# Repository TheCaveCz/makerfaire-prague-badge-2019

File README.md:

# MakerFaire Prague 2019 badge

Complete source code and schematics for MakerFaire Prague 2019 badges and other supporting devices.

*We are preparing more readme files, stay tuned*

## Few images

## Sponsorship

Badges were sponsored by [Seeed Studio](https://www.seeedstudio.com).

Výrobu badgů sponzorovalo [Seeed Studio](https://www.seeedstudio.com).

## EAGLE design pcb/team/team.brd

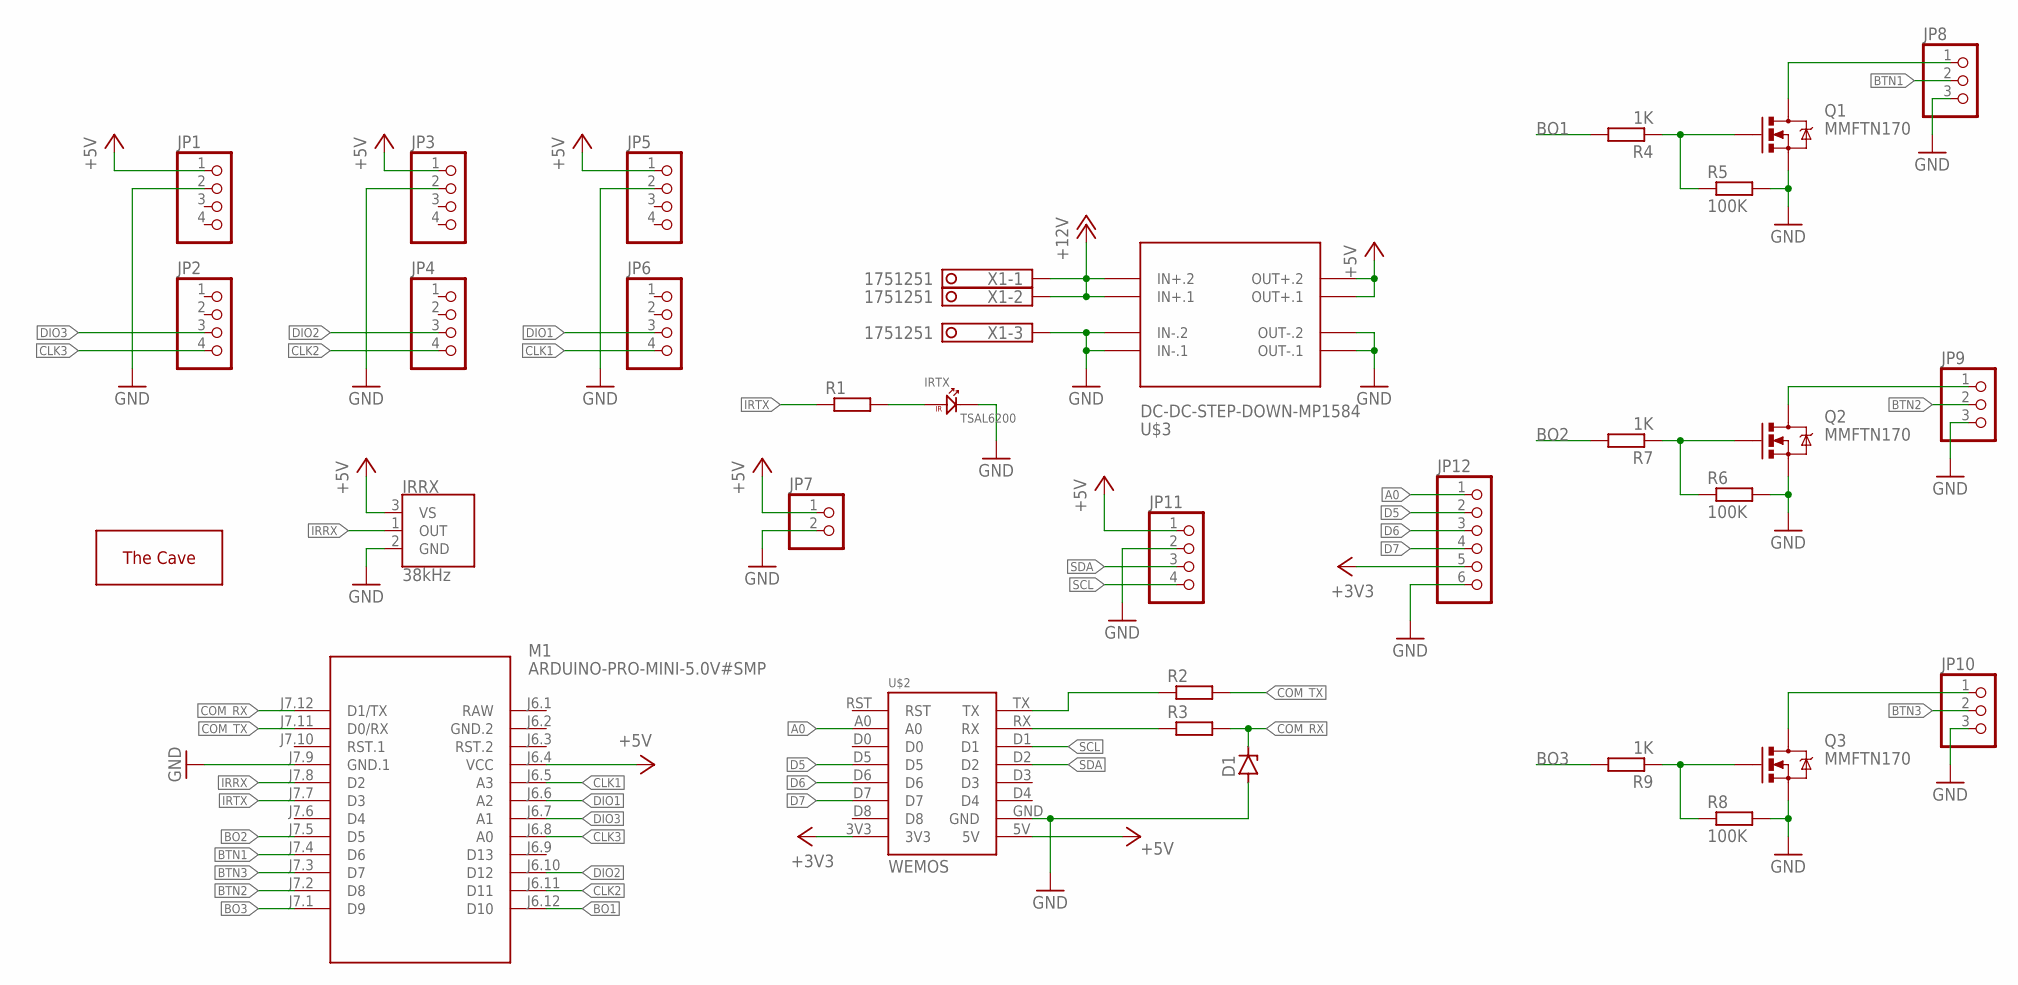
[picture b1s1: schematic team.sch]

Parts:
D1: ZENER-DIODEDO34-7; DO34Z7
IRRX: 38kHz; TSOP382
IRTX: TSAL6200
JP1, JP2, JP3, JP4, JP5, JP6, JP11: PINHD-1X4; 1X04
JP7: PINHD-1X2; 1X02
JP8, JP9, JP10: PINHD-1X3; 1X03
JP12: PINHD-1X6; 1X06
M1: ARDUINO-PRO-MINI-5.0V#SMP; ARDUINO-PRO-MINI#SMP
Q1, Q2, Q3: MMFTN170; SOT23-3
R1, R2, R3: R-EU_0207/7; 0207/7
R4, R7, R9: 1K; R0805
R5, R6, R8: 100K; R0805
U$1: THECAVE_LOGO_NEW_TOP; NEW_LOGO_TOP
U$2: WEMOS
U$3: DC-DC-STEP-DOWN-MP1584
X1: 1751251

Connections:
+3V3: JP12.5, U$2.3V3
+5V: IRRX.3 (VS), JP1.1, JP3.1, JP5.1, JP7.1, JP11.1, M1.J6.4 (VCC), U$2.5V, U$3.OUT+.1, U$3.OUT+.2
+12V: U$3.IN+.1, U$3.IN+.2, X1.1, X1.2
A0: JP12.1, U$2.A0
BO1: M1.J6.12 (D10), R4.2
BO2: M1.J7.5 (D5), R7.2
BO3: M1.J7.1 (D9), R9.2
BTN1: JP8.2, M1.J7.4 (D6)
BTN2: JP9.2, M1.J7.2 (D8)
BTN3: JP10.2, M1.J7.3 (D7)
CLK1: JP6.4, M1.J6.5 (A3)
CLK2: JP4.4, M1.J6.11 (D11)
CLK3: JP2.4, M1.J6.8 (A0)
COM_RX: D1.C, M1.J7.12 (D1/TX), R3.2
COM_TX: M1.J7.11 (D0/RX), R2.2
D5: JP12.2, U$2.D5
D6: JP12.3, U$2.D6
D7: JP12.4, U$2.D7
DIO1: JP6.3, M1.J6.6 (A2)
DIO2: JP4.3, M1.J6.10 (D12)
DIO3: JP2.3, M1.J6.7 (A1)
GND: D1.A, IRRX.2 (GND), IRTX.N, JP1.2, JP3.2, JP5.2, JP7.2, JP8.3, JP9.3, JP10.3, JP11.2, JP12.6, M1.J7.9 (GND.1), Q1.2 (S), Q2.2 (S), Q3.2 (S), R5.2, R6.2, R8.2, U$2.GND, U$3.IN-.1, U$3.IN-.2, U$3.OUT-.1, U$3.OUT-.2, X1.3
GND.2: M1.J6.2 (GND.2)
IRRX: IRRX.1 (OUT), M1.J7.8 (D2)
IRTX: M1.J7.7 (D3), R1.1
unnamed: R2.1, U$2.TX
unnamed: IRTX.P, R1.2
unnamed: R3.1, U$2.RX
unnamed: JP8.1, Q1.3 (D)
unnamed: Q1.1 (G), R4.1, R5.1
unnamed: JP9.1, Q2.3 (D)
unnamed: Q2.1 (G), R6.1, R7.1
unnamed: JP10.1, Q3.3 (D)
unnamed: Q3.1 (G), R8.1, R9.1
RAW: M1.J6.1 (RAW)
SCL: JP11.4, U$2.D1
SDA: JP11.3, U$2.D2

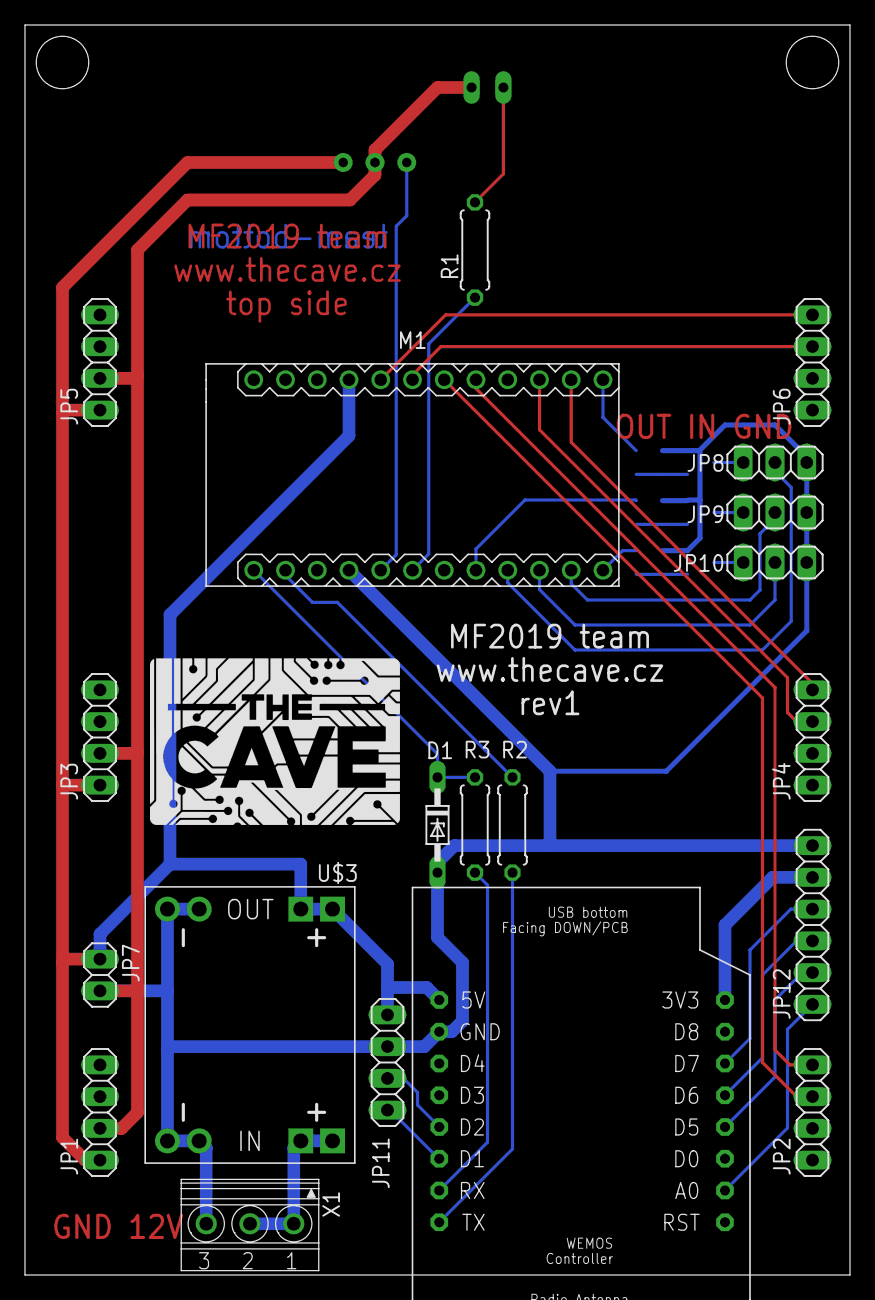
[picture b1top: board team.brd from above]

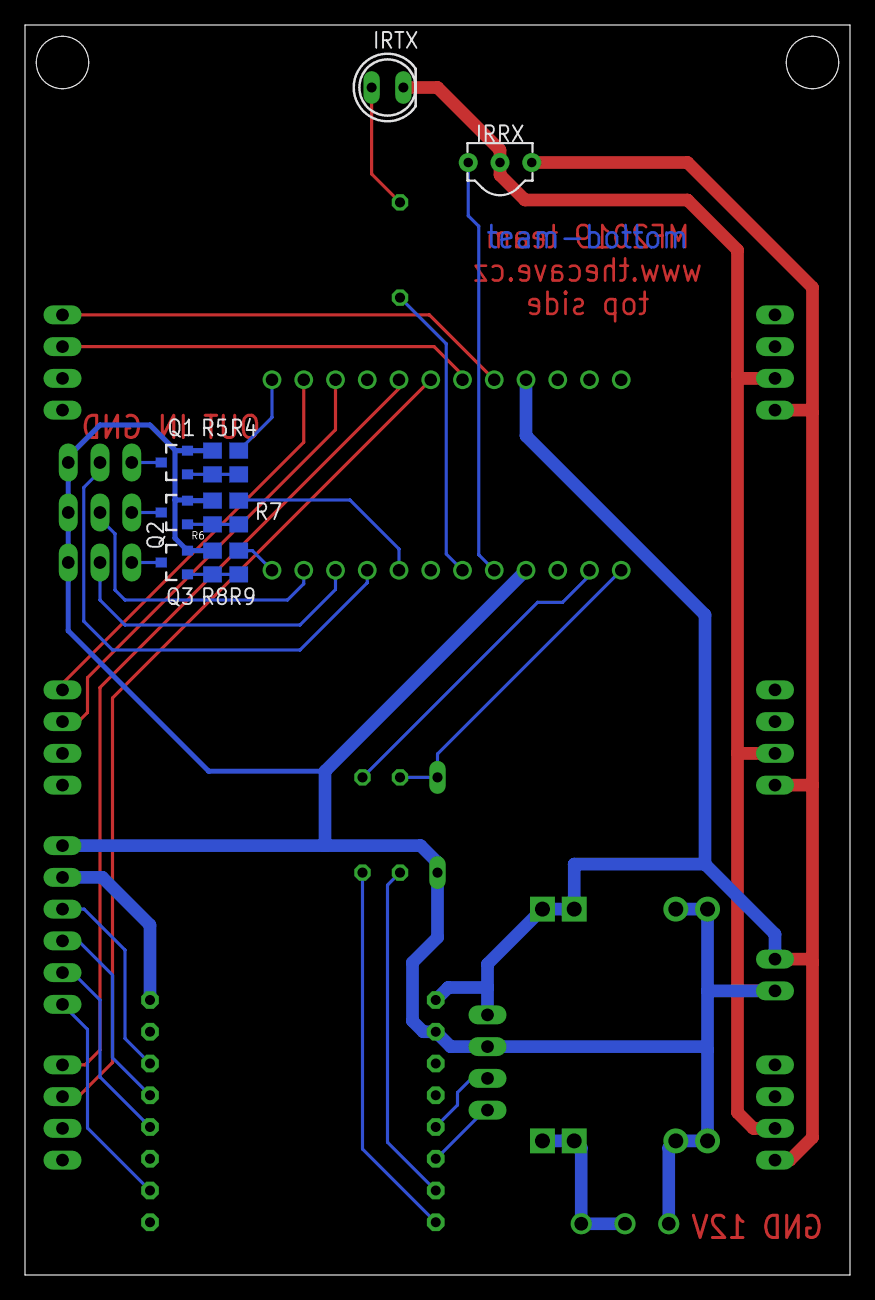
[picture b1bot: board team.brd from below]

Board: 2 copper layers, 66.0 x 100.0 mm, 32 parts (11 on the bottom side), 35 nets.

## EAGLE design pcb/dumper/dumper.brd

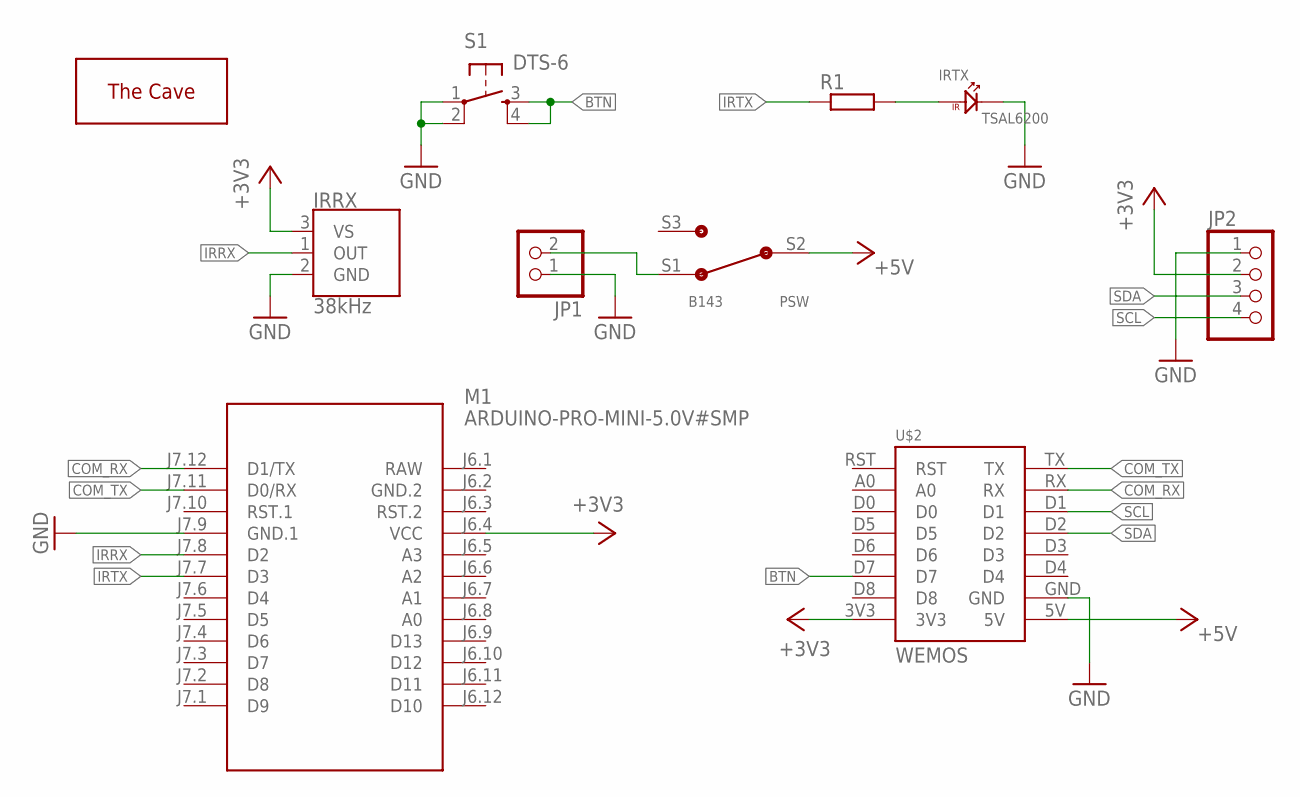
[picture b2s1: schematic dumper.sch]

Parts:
IRRX: 38kHz; TSOP382
IRTX: TSAL6200
JP1: PINHD-1X2; 1X02
JP2: PINHD-1X4; 1X04
M1: ARDUINO-PRO-MINI-5.0V#SMP; ARDUINO-PRO-MINI#SMP
PSW: B143
R1: R-EU_0207/7; 0207/7
S1: DTS-6
U$1: THECAVE_LOGO_NEW_TOP_SMALL; NEW_LOGO_SMALL_TOP
U$2: WEMOS

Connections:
+3V3: IRRX.3 (VS), JP2.2, M1.J6.4 (VCC), U$2.3V3
+5V: PSW.S2 (COM), U$2.5V
BTN: S1.3, S1.4, U$2.D7
COM_RX: M1.J7.12 (D1/TX), U$2.RX
COM_TX: M1.J7.11 (D0/RX), U$2.TX
GND: IRRX.2 (GND), IRTX.N, JP1.1, JP2.1, M1.J7.9 (GND.1), S1.1, S1.2, U$2.GND
GND.2: M1.J6.2 (GND.2)
IRRX: IRRX.1 (OUT), M1.J7.8 (D2)
IRTX: M1.J7.7 (D3), R1.1
unnamed: JP1.2, PSW.S1
unnamed: IRTX.P, R1.2
RAW: M1.J6.1 (RAW)
SCL: JP2.4, U$2.D1
SDA: JP2.3, U$2.D2

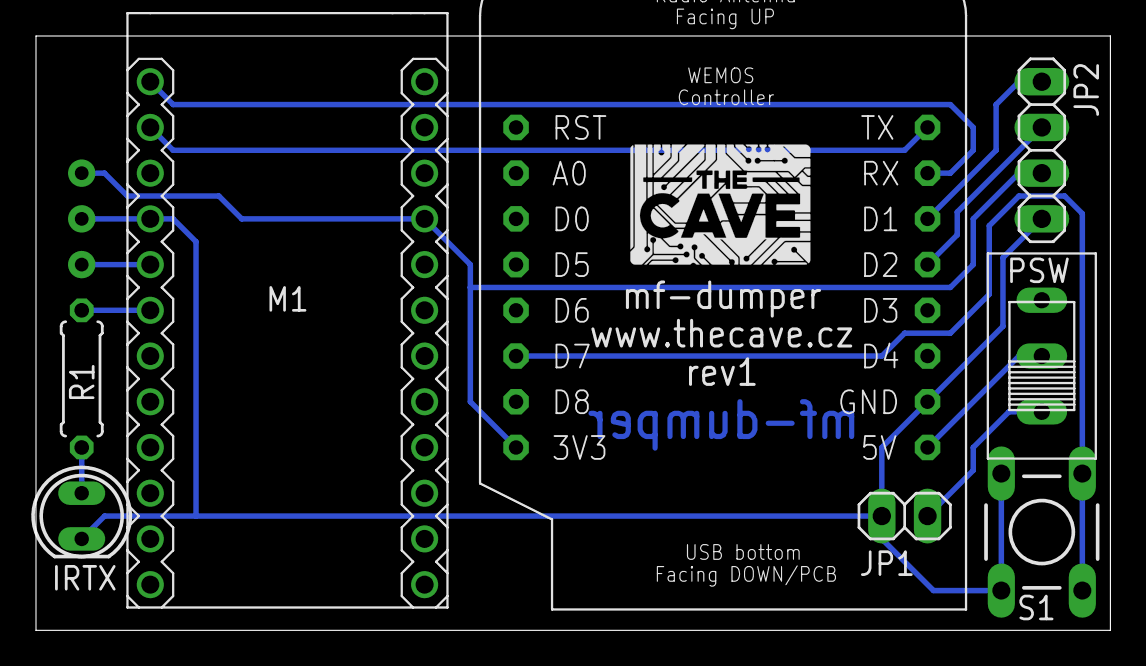
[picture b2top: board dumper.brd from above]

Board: 2 copper layers, 59.7 x 33.0 mm, 10 parts (1 on the bottom side), 12 nets.

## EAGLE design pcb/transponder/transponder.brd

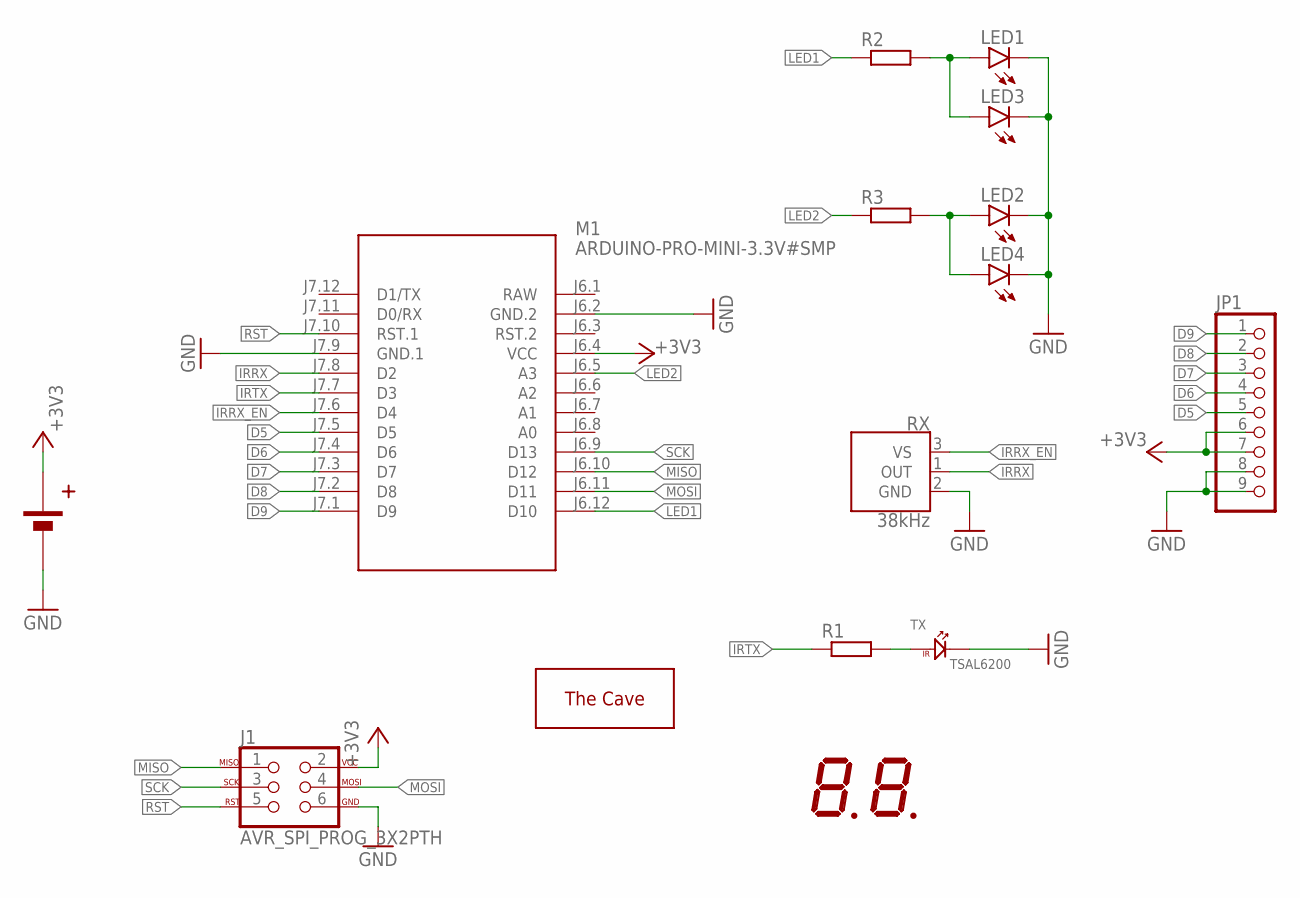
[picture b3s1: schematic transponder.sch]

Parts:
BAT1: BH-321-2P; 2AA_BATTERY
J1: AVR_SPI_PROG_3X2PTH; 2X3
JP1: PINHD-1X9; 1X09
LED1, LED2: LED5MM
LED3, LED4: LEDCHIPLED_1206; CHIPLED_1206
LED5, LED6: LCD_DIGIT
M1: ARDUINO-PRO-MINI-3.3V#SMP; ARDUINO-PRO-MINI#SMP
R1, R2, R3: R-EU_R0805; R0805
RX: 38kHz; TSOP382
TX: TSAL6200
U$1: THECAVE_LOGO_NEW_TOP_SMALL; NEW_LOGO_SMALL_TOP

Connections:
+3V3: BAT1.P$1 (VCC), J1.2, JP1.6, JP1.7, M1.J6.4 (VCC)
D5: JP1.5, M1.J7.5 (D5)
D6: JP1.4, M1.J7.4 (D6)
D7: JP1.3, M1.J7.3 (D7)
D8: JP1.2, M1.J7.2 (D8)
D9: JP1.1, M1.J7.1 (D9)
GND: BAT1.P$2 (GND), J1.6, JP1.8, JP1.9, LED1.K (C), LED2.K (C), LED3.C, LED4.C, M1.J6.2 (GND.2), M1.J7.9 (GND.1), RX.2 (GND), TX.N
IRRX: M1.J7.8 (D2), RX.1 (OUT)
IRRX_EN: M1.J7.6 (D4), RX.3 (VS)
IRTX: M1.J7.7 (D3), R1.1
LED1: M1.J6.12 (D10), R2.1
LED2: M1.J6.5 (A3), R3.1
MISO: J1.1, M1.J6.10 (D12)
MOSI: J1.4, M1.J6.11 (D11)
unnamed: R1.2, TX.P
unnamed: LED1.A, LED3.A, R2.2
unnamed: LED2.A, LED4.A, R3.2
RAW: M1.J6.1 (RAW)
RST: J1.5, M1.J7.10 (RST.1)
SCK: J1.3, M1.J6.9 (D13)

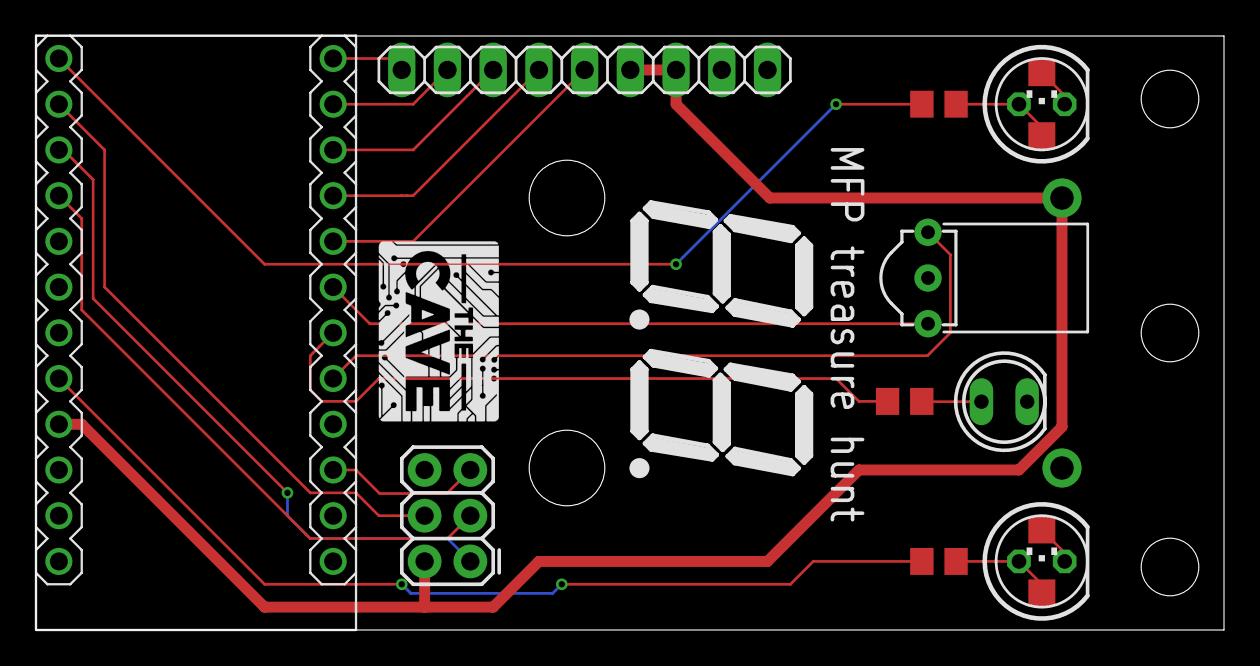
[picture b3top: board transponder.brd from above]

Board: 2 copper layers, 66.0 x 33.0 mm, 16 parts (1 on the bottom side), 19 nets.

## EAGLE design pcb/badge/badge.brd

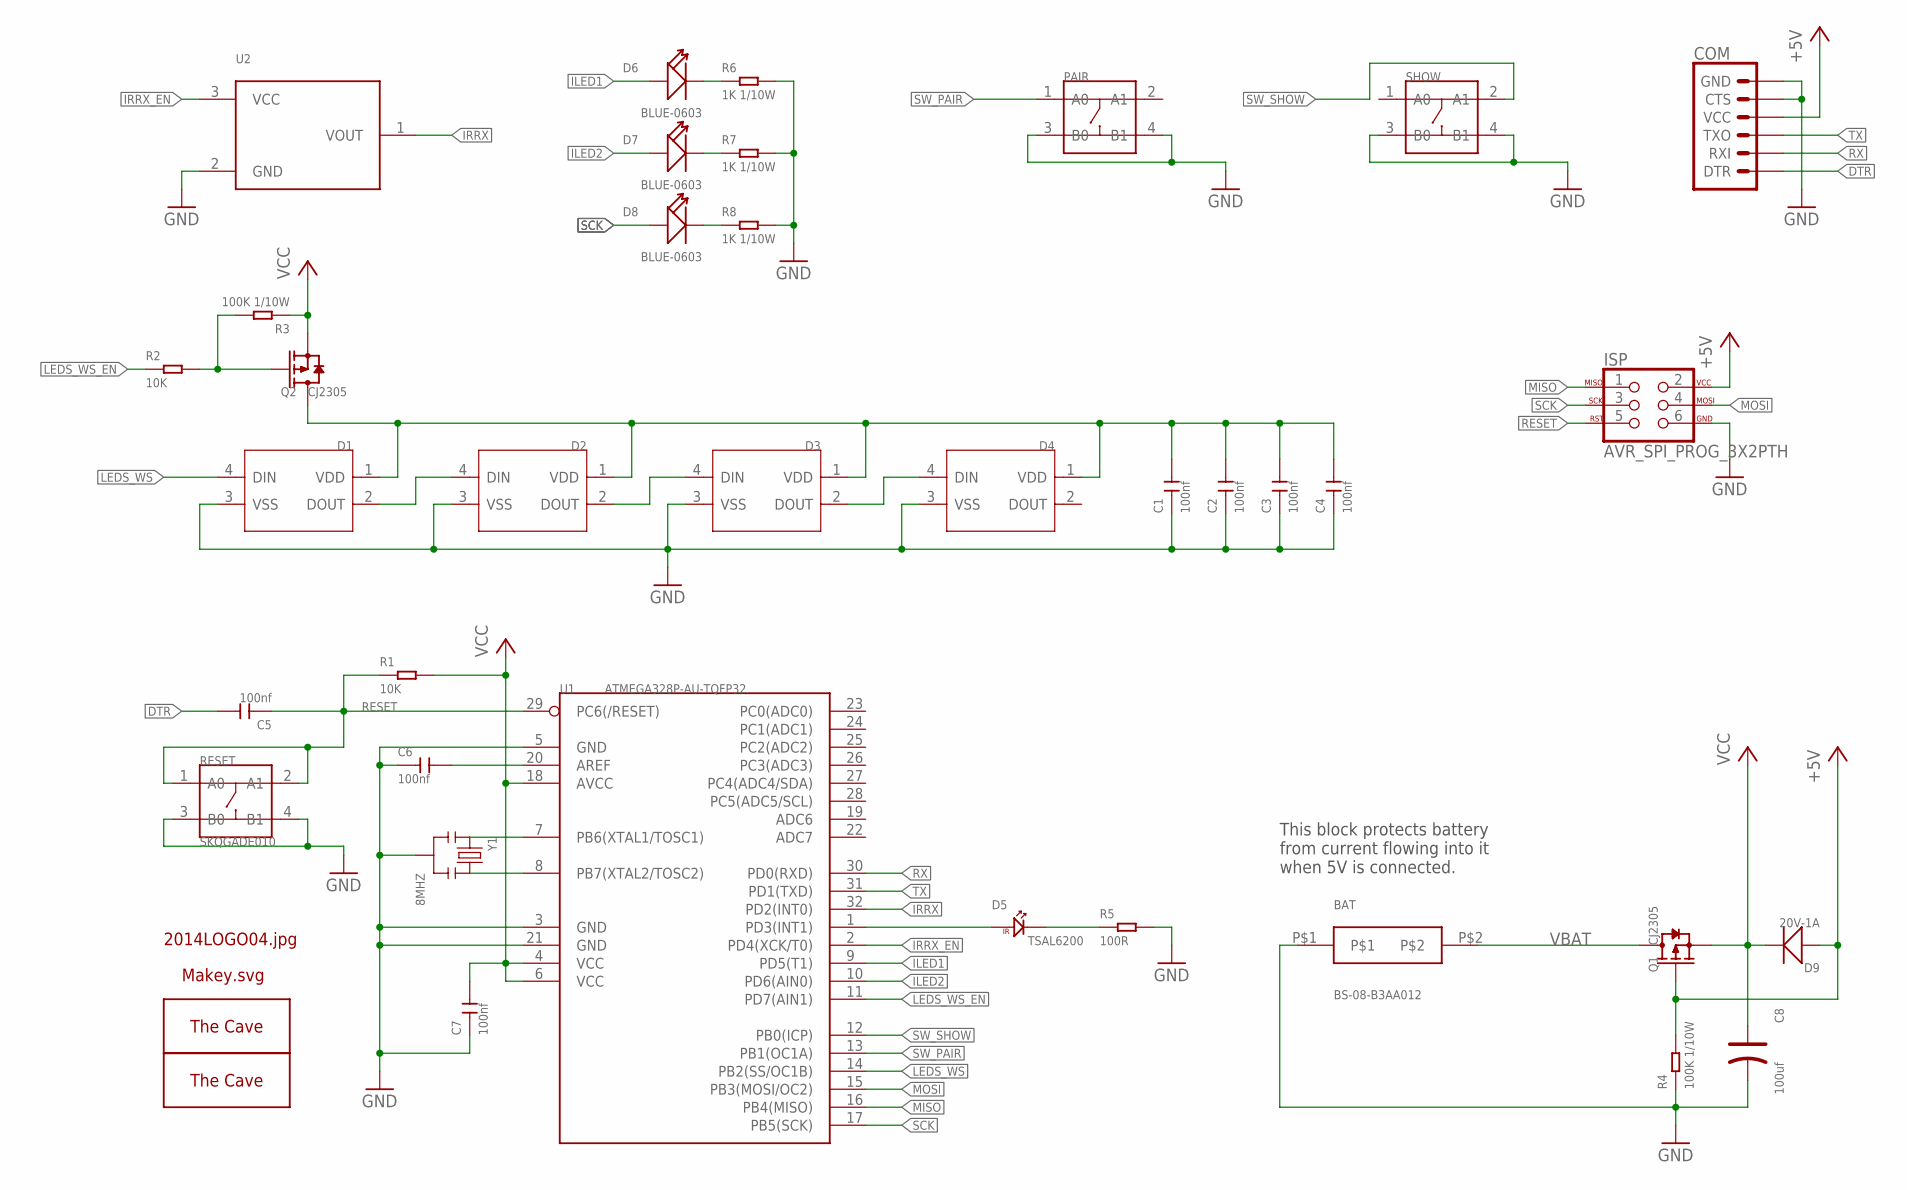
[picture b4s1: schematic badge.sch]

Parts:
BAT: BS-08-B3AA012; B3-08-B3AA012
C1, C2, C3, C4, C5, C6, C7: 100nf; C0603
C8: 100uf; AVX-B
COM: 6_PIN_SERIAL_TARGETSILK; 6_PIN_SERIAL_TARGET_SIDE_W_SILK
D1, D2, D3, D4: SMD-RGB-LED-4P'WS2812B'; LED4-SMD-5050
D5: TSAL6200
D6, D7, D8: BLUE-0603; LED-0603
D9: 20V-1A; SOD-123
ISP: AVR_SPI_PROG_3X2PTH; 2X3
PAIR: SMD-BUTTON(4P-5.2X5.2X1.5MM-SKQGADE010)-SKQGADE010; SW4-SMD-5.2X5.2X1.5MM
Q1, Q2: CJ2305; SOT-23
R1, R2: 10K; R0603
R3, R4: 100K 1/10W; R0603
R5: 100R; R0805
R6, R7, R8: 1K 1/10W; R0603
RESET: SKQGADE010; SW4-SMD-5.2X5.2X1.5MM
SHOW: SMD-BUTTON(4P-5.2X5.2X1.5MM-SKQGADE010)-SKQGADE010; SW4-SMD-5.2X5.2X1.5MM
U1: ATMEGA328P-AU-TQFP32; TQFP32-0.8-7X7MM
U2: TSOP382
U$1: 2014LOGO04#JPG
U$2: MAKEY#SVG
U$3: THECAVE_LOGO_NEW_TOP_SMALL; NEW_LOGO_SMALL_TOP
U$4: THECAVE_LOGO_NEW_COPPER_SMALL; NEW_LOGO_SMALL_COPPER
Y1: 8MHZ; X3-SMD-3.6X1.3X0.8MM

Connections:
+5V: COM.P$4 (VCC), D9.+, ISP.2, Q1.1 (G), R4.2
DTR: C5.2, COM.P$1 (DTR)
GND: BAT.P$1, C1.1, C2.1, C3.1, C4.1, C6.1, C7.1, C8.-, COM.P$5 (CTS), COM.P$6 (GND), D1.3 (VSS), D2.3 (VSS), D3.3 (VSS), D4.3 (VSS), ISP.6, PAIR.3 (B0), PAIR.4 (B1), R4.1, R5.2, R6.2, R7.2, R8.2, RESET.3 (B0), RESET.4 (B1), SHOW.3 (B0), SHOW.4 (B1), U1.3 (GND), U1.5 (GND), U1.21 (GND), U2.2 (GND), Y1.2
ILED1: D6.+, U1.9 (PD5(T1))
ILED2: D7.+, U1.10 (PD6(AIN0))
IRRX: U1.32 (PD2(INT0)), U2.1 (VOUT)
IRRX_EN: U1.2 (PD4(XCK/T0)), U2.3 (VCC)
LEDS_WS: D1.4 (DIN), U1.14 (PB2(SS/OC1B))
LEDS_WS_EN: R2.1, U1.11 (PD7(AIN1))
MISO: ISP.1, U1.16 (PB4(MISO))
MOSI: ISP.4, U1.15 (PB3(MOSI/OC2))
unnamed: D1.2 (DOUT), D2.4 (DIN)
unnamed: D2.2 (DOUT), D3.4 (DIN)
unnamed: D7.-, R7.1
unnamed: U1.7 (PB6(XTAL1/TOSC1)), Y1.1
unnamed: U1.8 (PB7(XTAL2/TOSC2)), Y1.3
unnamed: D5.N, R5.1
unnamed: C6.2, U1.20 (AREF)
unnamed: D6.-, R6.1
unnamed: D8.-, R8.1
unnamed: C1.2, C2.2, C3.2, C4.2, D1.1 (VDD), D2.1 (VDD), D3.1 (VDD), D4.1 (VDD), Q2.3 (D)
unnamed: D5.P, U1.1 (PD3(INT1))
unnamed: Q2.1 (G), R2.2, R3.2
unnamed: D3.2 (DOUT), D4.4 (DIN)
RESET: C5.1, ISP.5, R1.1, RESET.1 (A0), RESET.2 (A1), U1.29 (PC6(/RESET))
RX: COM.P$3 (RXI), U1.30 (PD0(RXD))
SCK: D8.+, ISP.3, U1.17 (PB5(SCK))
SW_PAIR: PAIR.1 (A0), U1.13 (PB1(OC1A))
SW_SHOW: SHOW.2 (A1), U1.12 (PB0(ICP))
TX: COM.P$2 (TXO), U1.31 (PD1(TXD))
VBAT: BAT.P$2, Q1.3 (D)
VCC: C7.2, C8.+, D9.-, Q1.2 (S), Q2.2 (S), R1.2, R3.1, U1.4 (VCC), U1.6 (VCC), U1.18 (AVCC)

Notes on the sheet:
This block protects battery from current flowing into it when 5V is connected.

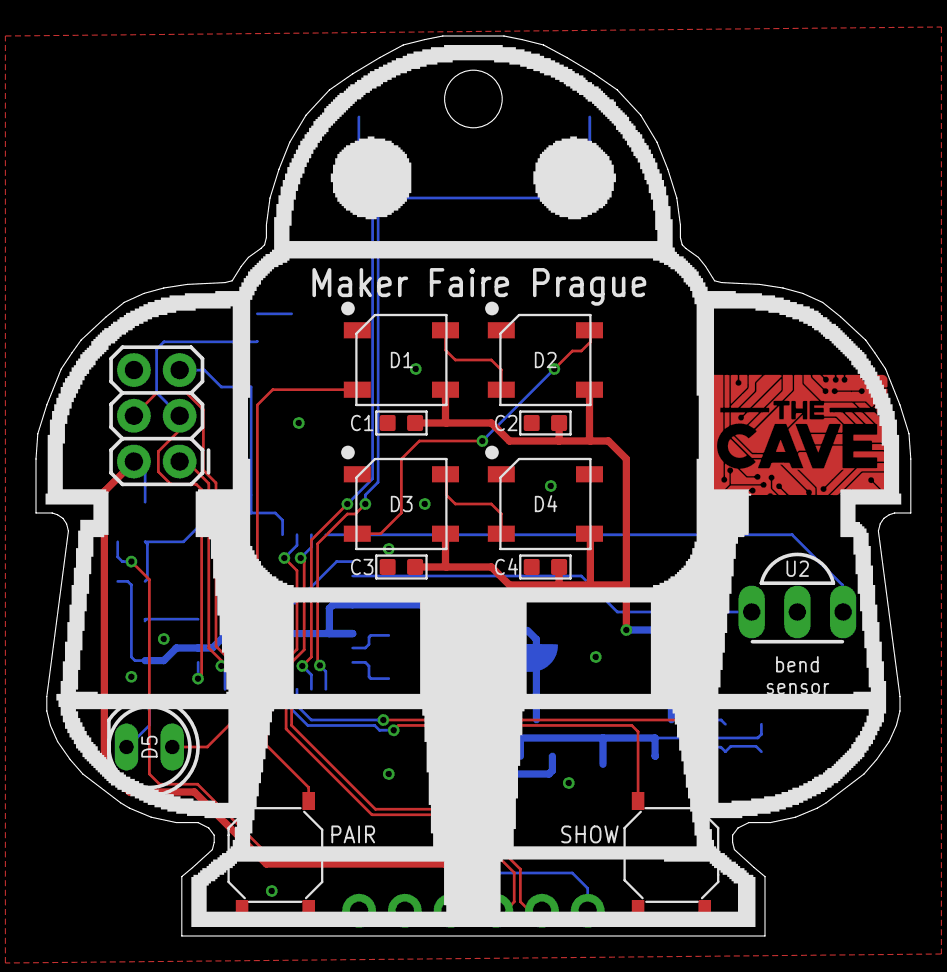
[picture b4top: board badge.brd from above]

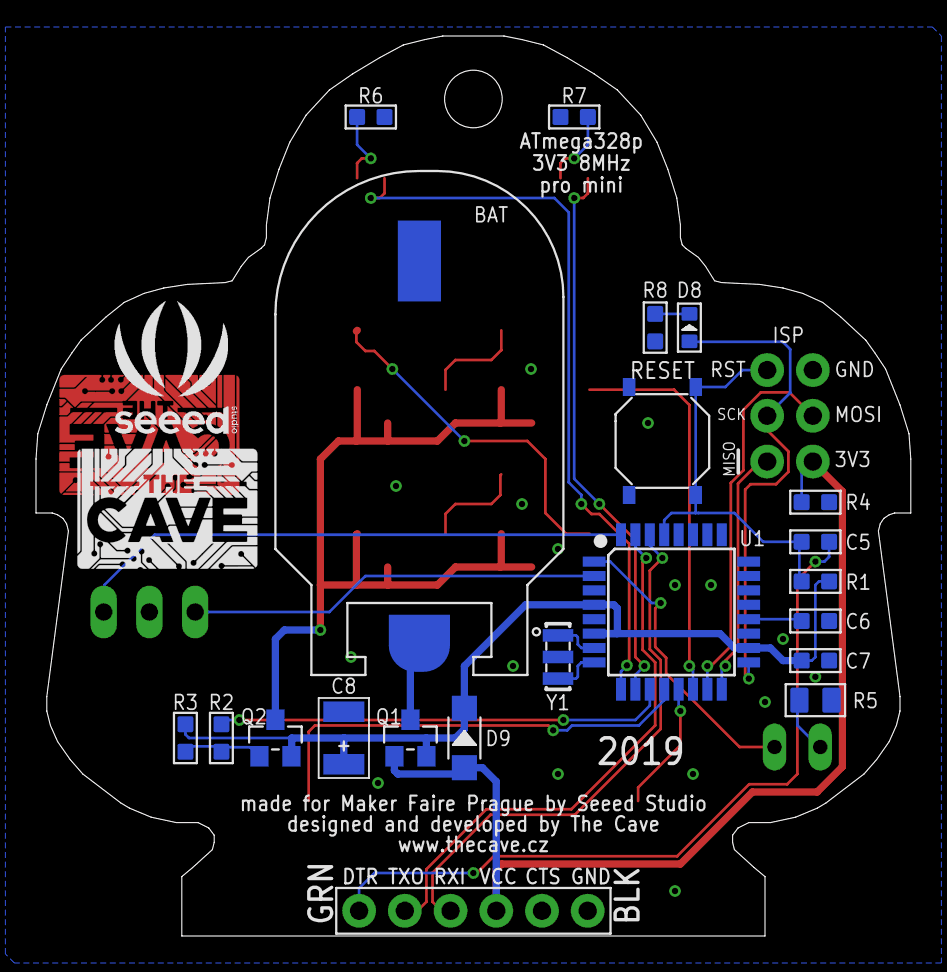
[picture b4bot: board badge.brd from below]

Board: 2 copper layers, 48.6 x 50.0 mm, 40 parts (23 on the bottom side), 32 nets.

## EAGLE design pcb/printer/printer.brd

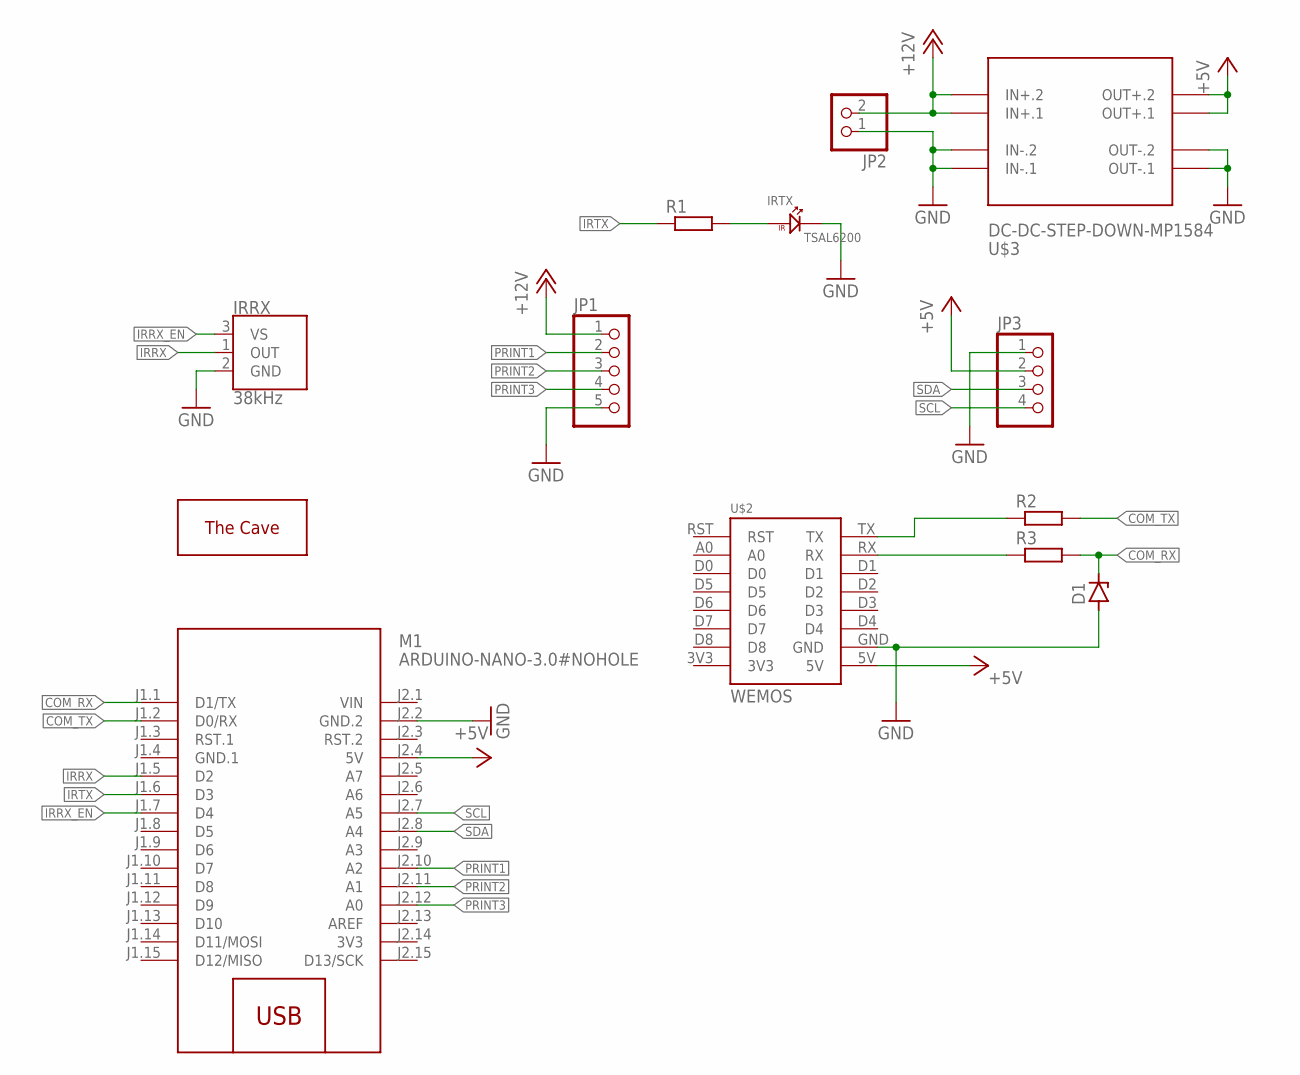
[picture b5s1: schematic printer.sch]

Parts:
D1: ZENER-DIODEDO34-7; DO34Z7
IRRX: 38kHz; TSOP382
IRTX: TSAL6200
JP1: PINHD-1X5; 1X05
JP2: PINHD-1X2; 1X02
JP3: PINHD-1X4; 1X04
M1: ARDUINO-NANO-3.0#NOHOLE; ARDUINO-NANO-3.0
R1, R2, R3: R-EU_0207/7; 0207/7
U$2: WEMOS
U$3: DC-DC-STEP-DOWN-MP1584
U$4: THECAVE_LOGO_NEW_BOTTOM; NEW_LOGO_BOTTOM

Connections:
3V3: M1.J2.14 (3V3)
+5V: JP3.2, M1.J2.4 (5V), U$2.5V, U$3.OUT+.1, U$3.OUT+.2
+12V: JP1.1, JP2.2, U$3.IN+.1, U$3.IN+.2
COM_RX: D1.C, M1.J1.1 (D1/TX), R3.2
COM_TX: M1.J1.2 (D0/RX), R2.2
GND: D1.A, IRRX.2 (GND), IRTX.N, JP1.5, JP2.1, JP3.1, M1.J2.2 (GND.2), U$2.GND, U$3.IN-.1, U$3.IN-.2, U$3.OUT-.1, U$3.OUT-.2
GND.1: M1.J1.4 (GND.1)
IRRX: IRRX.1 (OUT), M1.J1.5 (D2)
IRRX_EN: IRRX.3 (VS), M1.J1.7 (D4)
IRTX: M1.J1.6 (D3), R1.1
unnamed: R2.1, U$2.TX
unnamed: IRTX.P, R1.2
unnamed: R3.1, U$2.RX
PRINT1: JP1.2, M1.J2.10 (A2)
PRINT2: JP1.3, M1.J2.11 (A1)
PRINT3: JP1.4, M1.J2.12 (A0)
SCL: JP3.4, M1.J2.7 (A5)
SDA: JP3.3, M1.J2.8 (A4)
VIN: M1.J2.1 (VIN)

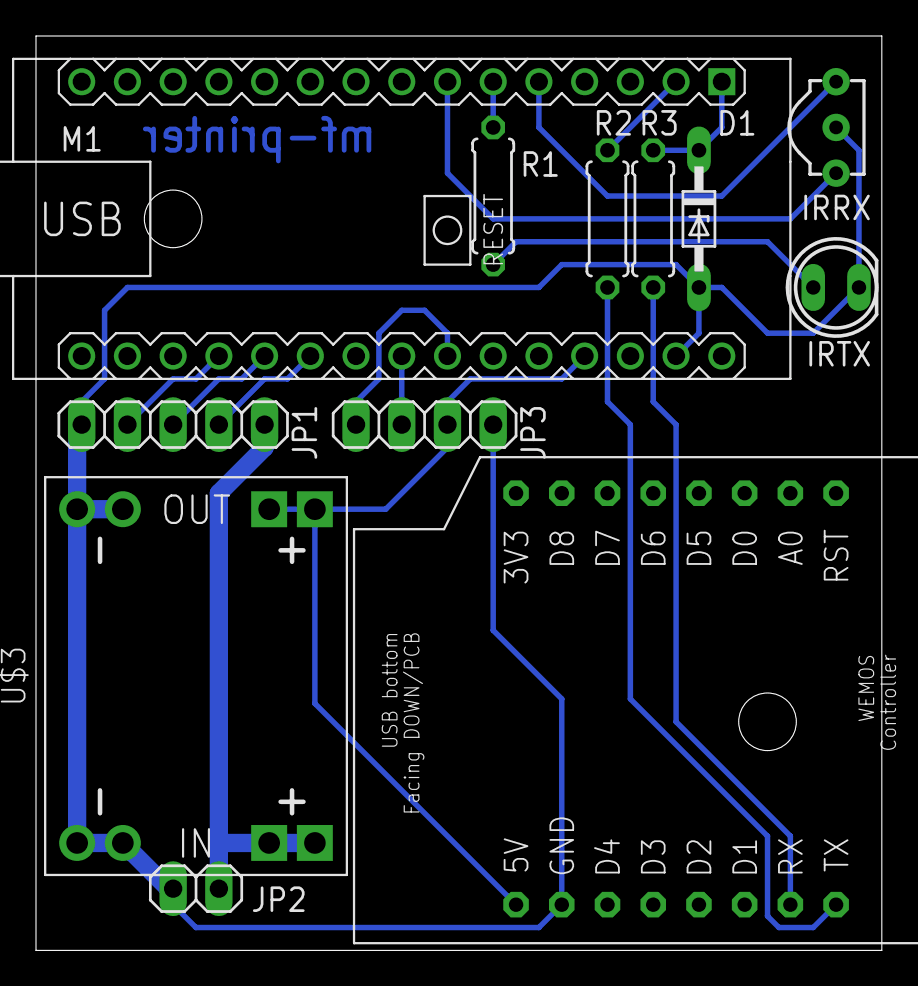
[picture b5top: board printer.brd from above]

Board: 2 copper layers, 47.0 x 50.8 mm, 13 parts (0 on the bottom side), 16 nets.

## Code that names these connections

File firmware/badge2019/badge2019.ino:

//////////////////////////////
//
// MakerFaire Prague 2019 badge
// (c) The Cave, 2019
// https://thecave.cz
//
// Licensed under MIT License.
//
//
// There are surely lot of ways how this code can be made better, but it works for the specific case we had.
// Lot of assumptions about sizes/commands/behaiours is hardcoded. If you change something, don't be
// surprised that it can break something else.
//
// Use "Arduino Pro or Pro Mini" board with "ATMega328P (3V3, 8MHz)" setting
//
// But if you change something and it works, feel free to send a pull request!
//
// Happy hacking!
//

#include <EEPROM.h>
#include <TaskScheduler.h>
#include <avr/sleep.h>
#include <avr/power.h>
#include <avr/interrupt.h>

// enable serial line debug info output
#define LOG_ENABLED 1

#define SERIAL_COMMANDS 1


// Pin Assignments

// PB2 (dip 16) output - data ouput line for WS2818 LEDS
#define PIN_LEDS_WS 10
// PD7 (dip 13) output - gate for P-MOSFET controlling WS2818 VCC line
#define PIN_LEDS_WS_ENABLE 7
// PD4 (dip 6) output - VCC for IR receiver
#define PIN_IRRX_EN 4
// PD2 (dip 4) input - data input line from IR receiver
#define PIN_IRRX 2
// PD3 (dip 5) output - IR led
#define PIN_IRTX 3
// PD6 (dip 12) output - left eye LED
#define PIN_LED1 6
// PD5 (dip 11) output - right eye LED
#define PIN_LED2 5
// PB5 builtin led - LED on the back of the robot
#define PIN_LED3 13

// both buttons need to be on the same port
// if you change pins you need to change the pin change interrupt regs too!
// PB1 (dip 15) input pullup - PAIR button
#define PIN_SW1 9
// PB0 (dip 14) input pullup - SHOW button
#define PIN_SW2 8


Scheduler scheduler;

// keep this function here otherwise this source will not compile!
void nothing() {}

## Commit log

2019-07-03 Add firmware
2019-07-03 Add drawings/3d prints
2019-07-03 Add upload scripts
2019-07-03 Add schematics
2019-07-03 Add basic readme

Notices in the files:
parts and their libraries:
SparkFun-Connectors: Licensing: Creative Commons ShareAlike 4.0 International - https://creativecommons.org/licenses/by-sa/4.0
diy-modules: Released under the Creative Commons Attribution 4.0 International License: http://creativecommons.org/licenses/by/4.0
